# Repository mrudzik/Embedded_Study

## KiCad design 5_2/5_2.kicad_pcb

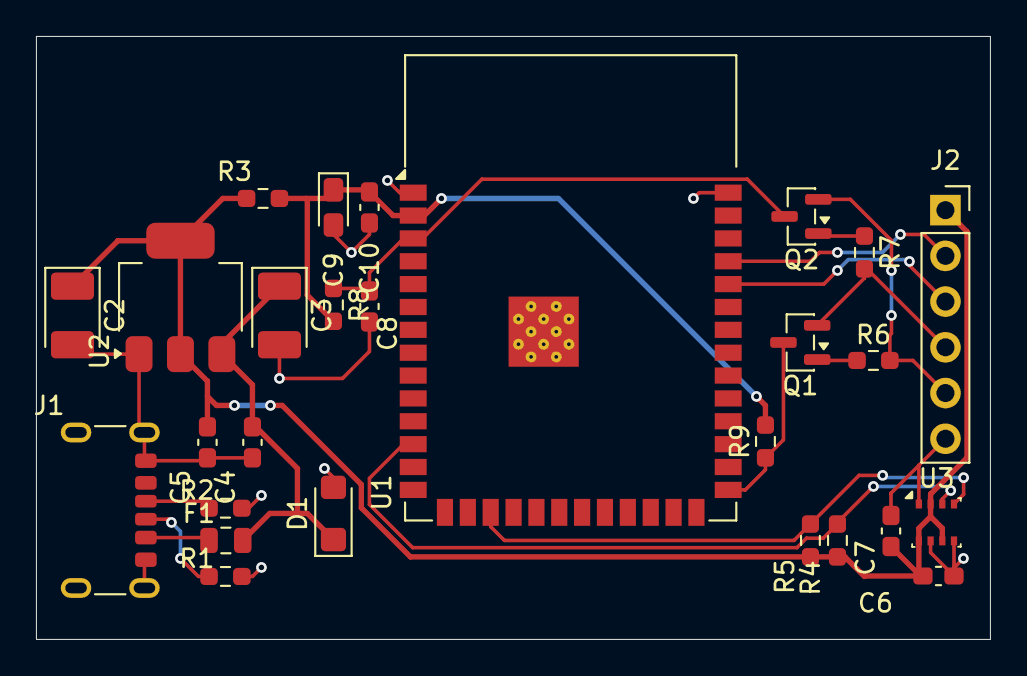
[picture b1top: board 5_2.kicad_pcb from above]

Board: 2 copper layers, 53.0 x 33.5 mm, 27 parts (0 on the bottom side), 17 nets.

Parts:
C2, C3: 22uF; CP_EIA-3528-21_Kemet-B_HandSolder
C4, C5, C8: 1uF; C_0603_1608Metric_Pad1.08x0.95mm_HandSolder
C6, C7, C10: 100nF; C_0603_1608Metric_Pad1.08x0.95mm_HandSolder
C9: 10uF; CP_EIA-2012-12_Kemet-R_HandSolder
D1: SMF6V0A; D_SMF
F1: 0.6A; Fuse_0805_2012Metric
J1: USB; USB_C_Receptacle_GCT_USB4125-xx-x-0190_6P_TopMnt_Horizontal
J2: PROGRAMING; PinSocket_1x06_P2.54mm_Vertical
Q1, Q2: MMBT3904; SOT-23
R1, R2: 5,1K; R_0603_1608Metric_Pad0.98x0.95mm_HandSolder
R3: 0; R_0603_1608Metric_Pad0.98x0.95mm_HandSolder
R4, R5: 4,7K; R_0603_1608Metric_Pad0.98x0.95mm_HandSolder
R6, R7, R8, R9: 10K; R_0603_1608Metric_Pad0.98x0.95mm_HandSolder
U1: ESP32-S3-WROOM-1
U2: AMS1117-3.3; SOT-223-3_TabPin2
U3: BME280; Bosch_LGA-8_2.5x2.5mm_P0.65mm_ClockwisePinNumbering

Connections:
+3V3: C2.1, C5.1, C6.1, C7.1, J2.1, R3.2, R4.1, R5.1, U2.2 (VO), U3.2 (CSB), U3.6 (VDDIO), U3.8 (VDD)
+5V: C3.1, C4.1, D1.1 (A1), F1.1, U2.3 (VI)
BOOT: Q1.3 (C), R9.1, U1.27 (IO0)
DTR: J2.4, Q1.2 (E), R7.2
EN: C8.1, Q2.3 (C), R8.1, U1.3 (EN)
ESP_RX: J2.3, U1.36 (RXD0)
ESP_TX: J2.2, U1.37 (TXD0)
GND: C2.2, C3.2, C4.2, C5.2, C6.2, C7.2, C8.2, C9.2, C10.2, D1.2 (A2), J1.A12 (GND), J1.B12 (GND), J1.SH (SHIELD), J2.6, R1.2, R2.2, U1.1 (GND), U1.40 (GND), U1.41 (GND), U2.1 (GND), U3.1 (GND), U3.5 (SDO), U3.7 (GND)
I2C_SCL: R5.2, U1.17 (IO9), U3.4 (SCK)
I2C_SDA: R4.2, U1.12 (IO8), U3.3 (SDI)
unnamed: F1.2, J1.A9 (VBUS), J1.B9 (VBUS)
unnamed: J1.A5 (CC1), R2.1
unnamed: J1.B5 (CC2), R1.1
unnamed: Q1.1 (B), R6.1
unnamed: Q2.1 (B), R7.1
RTS: J2.5, Q2.2 (E), R6.2
VDD: C9.1, C10.1, R3.1, R8.2, R9.2, U1.2 (3V3)
